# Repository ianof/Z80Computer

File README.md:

# Z80 Toggle-Switch Computer
A minimalistic computer using the Zilog Z80 microprocessor as an educational display.

The computer will be operated using the following controls:

  * 8 toggle-switches to specify an address in the RAM
  * 8 toggle-switches to enter data into the RAM
  * 8 LEDs to display the address bus
  * 8 LEDs to display the data bus
  * A potentiometer to control the clock speed
  * A toggle-switch to switch between running and writing to the RAM
  * A toggle-switch to switch between running continuously and single-stepping instructions
  * A button to step instructions
  * A button to read from the RAM
  * A button to write to the RAM

The computer will be in a laser-cut plywood housing. SolidWorks files for this can be found in the "Housing" folder.

A printed circuit board contains all the circuitry for the computer. Gerber files for this can be found in the "PCBFiles" folder. A schematic can be found in the "KiCad" folder.

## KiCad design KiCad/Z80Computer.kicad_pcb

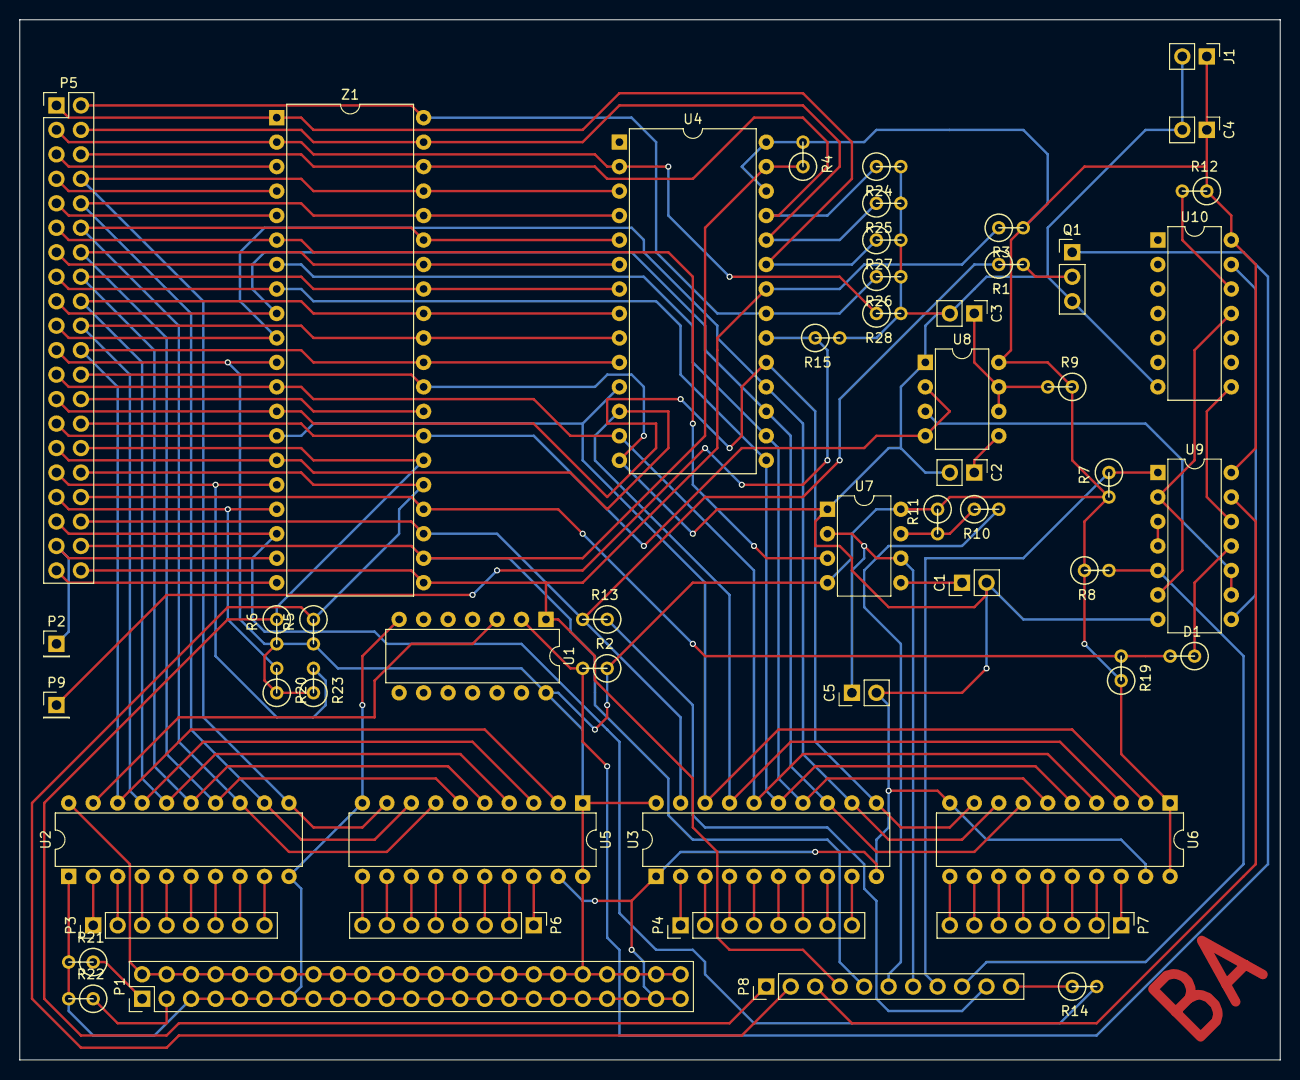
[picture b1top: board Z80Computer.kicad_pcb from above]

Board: 2 copper layers, 130.8 x 107.9 mm, 53 parts (0 on the bottom side), 96 nets.

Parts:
C1, C2, C3: 10nF; Pin_Header_Straight_1x02_Pitch2.54mm
C4, C5: 10uF; Pin_Header_Straight_1x02_Pitch2.54mm
D1: D; R1
J1: Screw_Terminal_Power_Input; Pin_Header_Straight_1x02_Pitch2.54mm
P1: CONN_02X23; Pin_Header_Straight_2x23_Pitch2.54mm
P2, P9: CONN_01X01; Pin_Header_Straight_1x01_Pitch2.54mm
P3, P4, P6, P7: CONN_01X08; Pin_Header_Straight_1x08_Pitch2.54mm
P5: CONN_02X20; Pin_Header_Straight_2x20_Pitch2.54mm
P8: CONN_01X11; Pin_Header_Straight_1x11_Pitch2.54mm
Q1: Q_NPN_CBE; Pin_Header_Straight_1x03_Pitch2.54mm
R1: 100k; R1
R2, R3, R4, R5, R6, R7, R8, R9, R11, R12, R15, R19, R20, R23, R24, R25, R26, R27, R28: 10k; R1
R10: 3.3k; R1
R13, R14: 220; R1
R21, R22: 630; R1
U1, U9: 7400; DIP-14_W7.62mm
U2, U3, U5, U6: SN74LVC245A; DIP-20_W7.62mm
U4: AS6C6264; DIP-28_W15.24mm
U7, U8: NE555; DIP-8_W7.62mm
U10: 74LS74; DIP-14_W7.62mm
Z1: Z80; DIP-40_W15.24mm

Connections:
BUSACK: P5.36, R1.1, R13.2, U3.19, Z1.23
BUSRQ: P5.32, P8.2, R5.1, Z1.25
CLK: P5.11, U7.3, Z1.6
GND: C1.2, C2.2, C3.2, C4.2, C5.2, J1.2, P1.5, P1.7, P1.9, P1.11, P1.13, P1.15, P1.17, P1.19, P1.21, P1.23, P1.25, P1.27, P1.29, P1.31, P1.33, P1.35, P1.37, P1.39, P1.41, P1.43, P1.45, P5.24, Q1.3, R15.2, R21.2, R22.2, R24.2, R25.2, R26.2, R27.2, R28.2, U1.7, U2.1, U2.10, U3.1, U3.10, U4.14, U5.10, U5.19, U6.10, U6.19, U7.1, U8.1, U9.7, U10.7, Z1.29
HALT: P5.35, R14.2, Z1.18
INT: P5.31, R23.2, Z1.16
IOREQ: P5.39, Z1.20
M1: P5.28, U8.2, U8.4, Z1.27
MREQ: P2.1, P5.37, Z1.19
NMI: P5.33, R20.2, Z1.17
unnamed: C1.1, U7.5
unnamed: C2.1, U8.5
unnamed: C3.1, R9.2, U8.6, U8.7
unnamed: C5.1, P8.7, U7.2, U7.6
unnamed: D1.1, U9.11
unnamed: P1.1, R21.1
unnamed: P1.3, R22.1
unnamed: P3.1, U2.2
unnamed: P3.2, U2.3
unnamed: P3.3, U2.4
unnamed: P3.4, U2.5
unnamed: P3.5, U2.6
unnamed: P3.6, U2.7
unnamed: P3.7, U2.8
unnamed: P3.8, U2.9
unnamed: P4.1, U3.2
unnamed: P4.2, U3.3
unnamed: P4.3, U3.4
unnamed: P4.4, U3.5
unnamed: P4.5, U3.6
unnamed: P4.6, U3.7
unnamed: P4.7, U3.8
unnamed: P4.8, U3.9
unnamed: P5.1, R27.1, U4.23, Z1.1
unnamed: P5.2, R26.1, U4.21, Z1.40
unnamed: P5.3, R28.1, U4.2, Z1.2
unnamed: P5.4, R25.1, U4.24, Z1.39
unnamed: P5.5, Z1.3
unnamed: P5.6, R24.1, U4.25, Z1.38
unnamed: P5.7, Z1.4
unnamed: P5.8, U2.11, U4.3, U5.9, Z1.37
unnamed: P5.9, Z1.5
unnamed: P5.10, U2.12, U4.4, U5.8, Z1.36
unnamed: P5.12, U2.13, U4.5, U5.7, Z1.35
unnamed: P5.13, U3.14, U4.16, U6.6, Z1.7
unnamed: P5.14, U2.14, U4.6, U5.6, Z1.34
unnamed: P5.15, U3.15, U4.15, U6.5, Z1.8
unnamed: P5.16, U2.15, U4.7, U5.5, Z1.33
unnamed: P5.17, U3.13, U4.17, U6.7, Z1.9
unnamed: P5.18, U2.16, U4.8, U5.4, Z1.32
unnamed: P5.19, U3.12, U4.18, U6.8, Z1.10
unnamed: P5.20, U2.17, U4.9, U5.3, Z1.31
unnamed: P5.22, U2.18, U4.10, U5.2, Z1.30
unnamed: P5.23, U3.16, U4.13, U6.4, Z1.12
unnamed: P5.25, U3.11, U4.19, U6.9, Z1.13
unnamed: P5.27, U3.18, U4.11, U6.2, Z1.14
unnamed: P5.29, U3.17, U4.12, U6.3, Z1.15
unnamed: P6.1, U5.18
unnamed: P6.2, U5.17
unnamed: P6.3, U5.16
unnamed: P6.4, U5.15
unnamed: P6.5, U5.14
unnamed: P6.6, U5.13
unnamed: P6.7, U5.12
unnamed: P6.8, U5.11
unnamed: P7.1, U6.18
unnamed: P7.2, U6.17
unnamed: P7.3, U6.16
unnamed: P7.4, U6.15
unnamed: P7.5, U6.14
unnamed: P7.6, U6.13
unnamed: P7.7, U6.12
unnamed: P7.8, U6.11
unnamed: P8.3, U9.13
unnamed: P8.6, R10.2
unnamed: P8.8, R7.1, U9.1
unnamed: P8.9, R8.2, U9.5
unnamed: P8.10, R13.1
unnamed: P8.11, R14.1
unnamed: P9.1, R15.1, U4.20
unnamed: Q1.1, R2.2, U1.2
unnamed: Q1.2, R1.2
unnamed: R10.1, R11.2, U7.7
unnamed: R12.2, U10.12
unnamed: U1.3, U2.19
unnamed: U8.3, U9.9, U9.10
unnamed: U9.3, U9.4
unnamed: U9.12, U10.8
unnamed: U9.2, U9.6, U10.11
unnamed: U9.8, U10.13
RD: P5.40, P8.4, R3.1, U1.1, U4.22, Z1.21
RESET: P5.30, P8.1, R6.1, Z1.26
RFSH: P5.26, Z1.28
VCC: C4.1, J1.1, P1.2, P1.4, P1.6, P1.8, P1.10, P1.12, P1.14, P1.16, P1.18, P1.20, P1.22, P1.24, P1.26, P1.28, P1.30, P1.32, P1.34, P1.36, P1.38, P1.40, P1.42, P1.44, P1.46, P5.21, R2.1, R3.2, R4.2, R5.2, R6.2, R7.2, R8.1, R9.1, R11.1, R12.1, R19.1, R20.1, R23.1, U1.14, U2.20, U3.20, U4.26, U4.28, U5.1, U5.20, U6.1, U6.20, U7.4, U7.8, U8.8, U9.14, U10.14, Z1.11
WAIT: D1.2, P5.34, R19.2, Z1.24
WR: P5.38, P8.5, R4.1, U4.27, Z1.22

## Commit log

2017-05-31 Added PCB Files
2017-05-31 Reorganizing
2017-05-31 Added housing files
2017-06-01 no message
